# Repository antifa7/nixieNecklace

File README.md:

# nixieNecklace
nixie necklace on the cheap using IN-19 tubes and disposable camera flash circuit components.

Here is the working file where I will be listing components and instructions on how to make this necklace.

Until I find out what brand and model specifically you want to use, the cameras that work the best either are the ones with only one transistor on the board, do not have any SMD components and hace a smaller transformer with 5 or six pins. I have seen some with 8 pins and have a larger package and footprint. The transformer is 8mm x 9mm x 9 mm high. The transistor has the marking 2SD2470 and I've seen some with D965. The diode is black. Some flashes only have one diode and others I have seen have two. When a second one is present, it is glass. You don't want that.

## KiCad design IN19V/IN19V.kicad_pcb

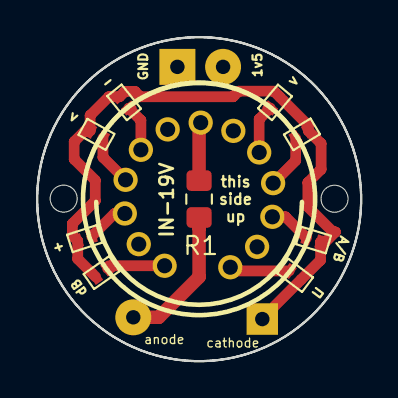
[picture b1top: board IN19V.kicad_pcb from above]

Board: 2 copper layers, 18.0 x 18.0 mm, 13 parts (0 on the bottom side), 10 nets.

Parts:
1v5: 1v5; SolderWirePad_1x01_Drill0.8mm
+: SolderJumper-2 nixieNecklace; SolderJumper-2-NixieNecklace
-: SolderJumper-2 nixieNecklace; SolderJumper-2-NixieNecklace
<: SolderJumper-2 nixieNecklace; SolderJumper-2-NixieNecklace
>: SolderJumper-2 nixieNecklace; SolderJumper-2-NixieNecklace
A/B: SolderJumper-2 nixieNecklace; SolderJumper-2-NixieNecklace
GND: GND; SolderWirePad_1x01_Drill0.8mm
N1: IN-19V; IN-19
R1: R; R_0805_2012Metric_Pad1.15x1.40mm_HandSolder
anode: anode; SolderWirePad_1x01_Drill0.8mm
cathode: cathode; SolderWirePad_1x01_Drill0.8mm
dB: SolderJumper-2 nixieNecklace; SolderJumper-2-NixieNecklace
Π: SolderJumper-2 nixieNecklace; SolderJumper-2-NixieNecklace

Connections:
unnamed: R1.1, anode.1
unnamed: +.2, -.2, <.2, >.2, A/B.2, cathode.1, dB.2, Π.2
unnamed: N1.2, Π.1
unnamed: A/B.1, N1.4
unnamed: <.1, N1.6
unnamed: N1.8, R1.2
unnamed: -.1, N1.10
unnamed: >.1, N1.11
unnamed: +.1, N1.12
unnamed: N1.14, dB.1

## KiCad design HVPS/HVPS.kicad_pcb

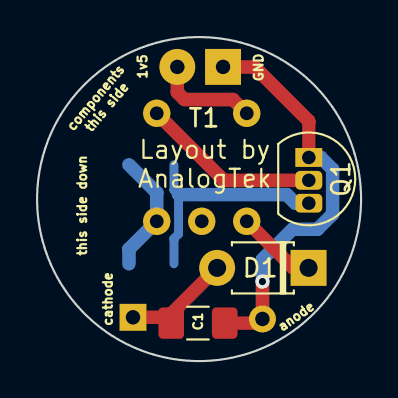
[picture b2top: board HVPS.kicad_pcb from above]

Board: 2 copper layers, 18.0 x 18.0 mm, 9 parts (1 on the bottom side), 7 nets.

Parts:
1v5: 1v5; SolderWirePad_1x01_Drill0.8mm
C1: 2.2uF 250v; C_1206_3216Metric_Pad1.42x1.75mm_HandSolder
D1: F16V27; D_T-1_P5.08mm_Horizontal
GND: GND in; SolderWirePad_1x01_Drill0.8mm
Q1: 2SD2470; TO-92L_Inline
T1: Flash XFMR; XFT-5383
anode: HV out; SolderWirePad_1x01_Drill0.8mm
cathode: GND out; SolderWirePad_1x01_Drill0.8mm
switch: MSS22D18D

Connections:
+1V5: 1v5.1, T1.1
GND: C1.2, GND.1, Q1.1, anode.1
unnamed: D1.1, T1.4
unnamed: Q1.2, T1.2
unnamed: Q1.3, switch.1
unnamed: T1.3, switch.2
VCC: C1.1, D1.2, cathode.1

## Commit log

2020-11-15 Add files via upload
    15 NOV 2020 11:06 PM changed trace width from .25mm to .4 - .75mm.
